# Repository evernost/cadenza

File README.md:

# cadenza
A reactive tachometer for bike.

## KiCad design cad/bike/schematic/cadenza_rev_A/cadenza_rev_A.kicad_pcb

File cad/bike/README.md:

# Cadenza project

A tachometer with reactive display (bike version)

---

## Overview

- **Type:** 
- **Domain:** Digital
- **Status:** Work in progress

---

## Features
This is an attempt to make a bike tachometer with a display providing a much better FPS compared to most tachometers you can find. 
Most of them are incredibly sluggish for reasons that are beyond me.

---

## Interfaces

### Inputs
| Name | Type | Range | Description |
|-----|------|-------|-------------|

### Outputs
| Name | Type | Description |
|------|------|-------------|
| OUT | Audio | Filtered signal |

---

## Controls

| Control | Type | Description |
|--------|------|-------------|
| Cutoff | Potentiometer | Manual cutoff frequency |
| Resonance | Potentiometer | Feedback amount |

---

## Electrical Characteristics

- **Supply voltage:** ±12V
- **Current consumption:** TBD mA
- **Signal levels:** TBD

---

## Implementation Notes
Section is TODO.

---

## Files

| File                          | Description                       |
|-------------------------------|-----------------------------------|
| `playLight_rev_A.pdf`         | Electrical schematic (PDF export) |
| `playLight_rev_A.kicad_sch`   | Schematic (KiCad 9.0.7)           |
| `playLight_rev_A.kicad_pcb`   | PCB layout (KiCad 9.0.7)          |
| `/production`                 | Production files (Gerbers + .zip) |

---

## Calibration / Tuning
None.

---

## Known Issues / TODO
None.

---

## Revision History

| Revision | Date | Notes |
|--------|------|-------|
| Rev A | 2026-06-20 | Initial prototype without USB support |
| Rev B | YYYY-MM-DD | Second version with USB logging |

---

## Tools
Designed with KiCAD 9.0.7

Grid dimensions

| Name   | Size    | Description        |
|--------|---------|--------------------|
| Grid 1 | 0.25 mm | PCB outline        |
| Grid 2 | 25 mil  | parts placement    |
| Grid 3 | 10 mil  | routing            |

---

## Related Modules
None.

---

## References
| Part type          | Reference                                                                                            | Selection criteria |
|--------------------|------------------------------------------------------------------------------------------------------|--------------------|
| LED driver         | TLC591 (TI)                                                                                          | Available in KiCAD<br>At least 8 outputs<br>Daisy-chain support |
| 7 segments display | HDSP-A401 (orange variant)<br>HDSP-7501 (red variant, high efficiency)<br>HDSP-7801 (green variant)  | Available in KiCAD<br> Bright enough for outside readbility|
| MCU                | STM32F098                                                                                            | USB OTG (for flash drive support)<br>Low pin count (for size)<br>3.3V supply|
| ON/OFF switch      | GW12LJPD                                                                                             | Available in KiCAD |

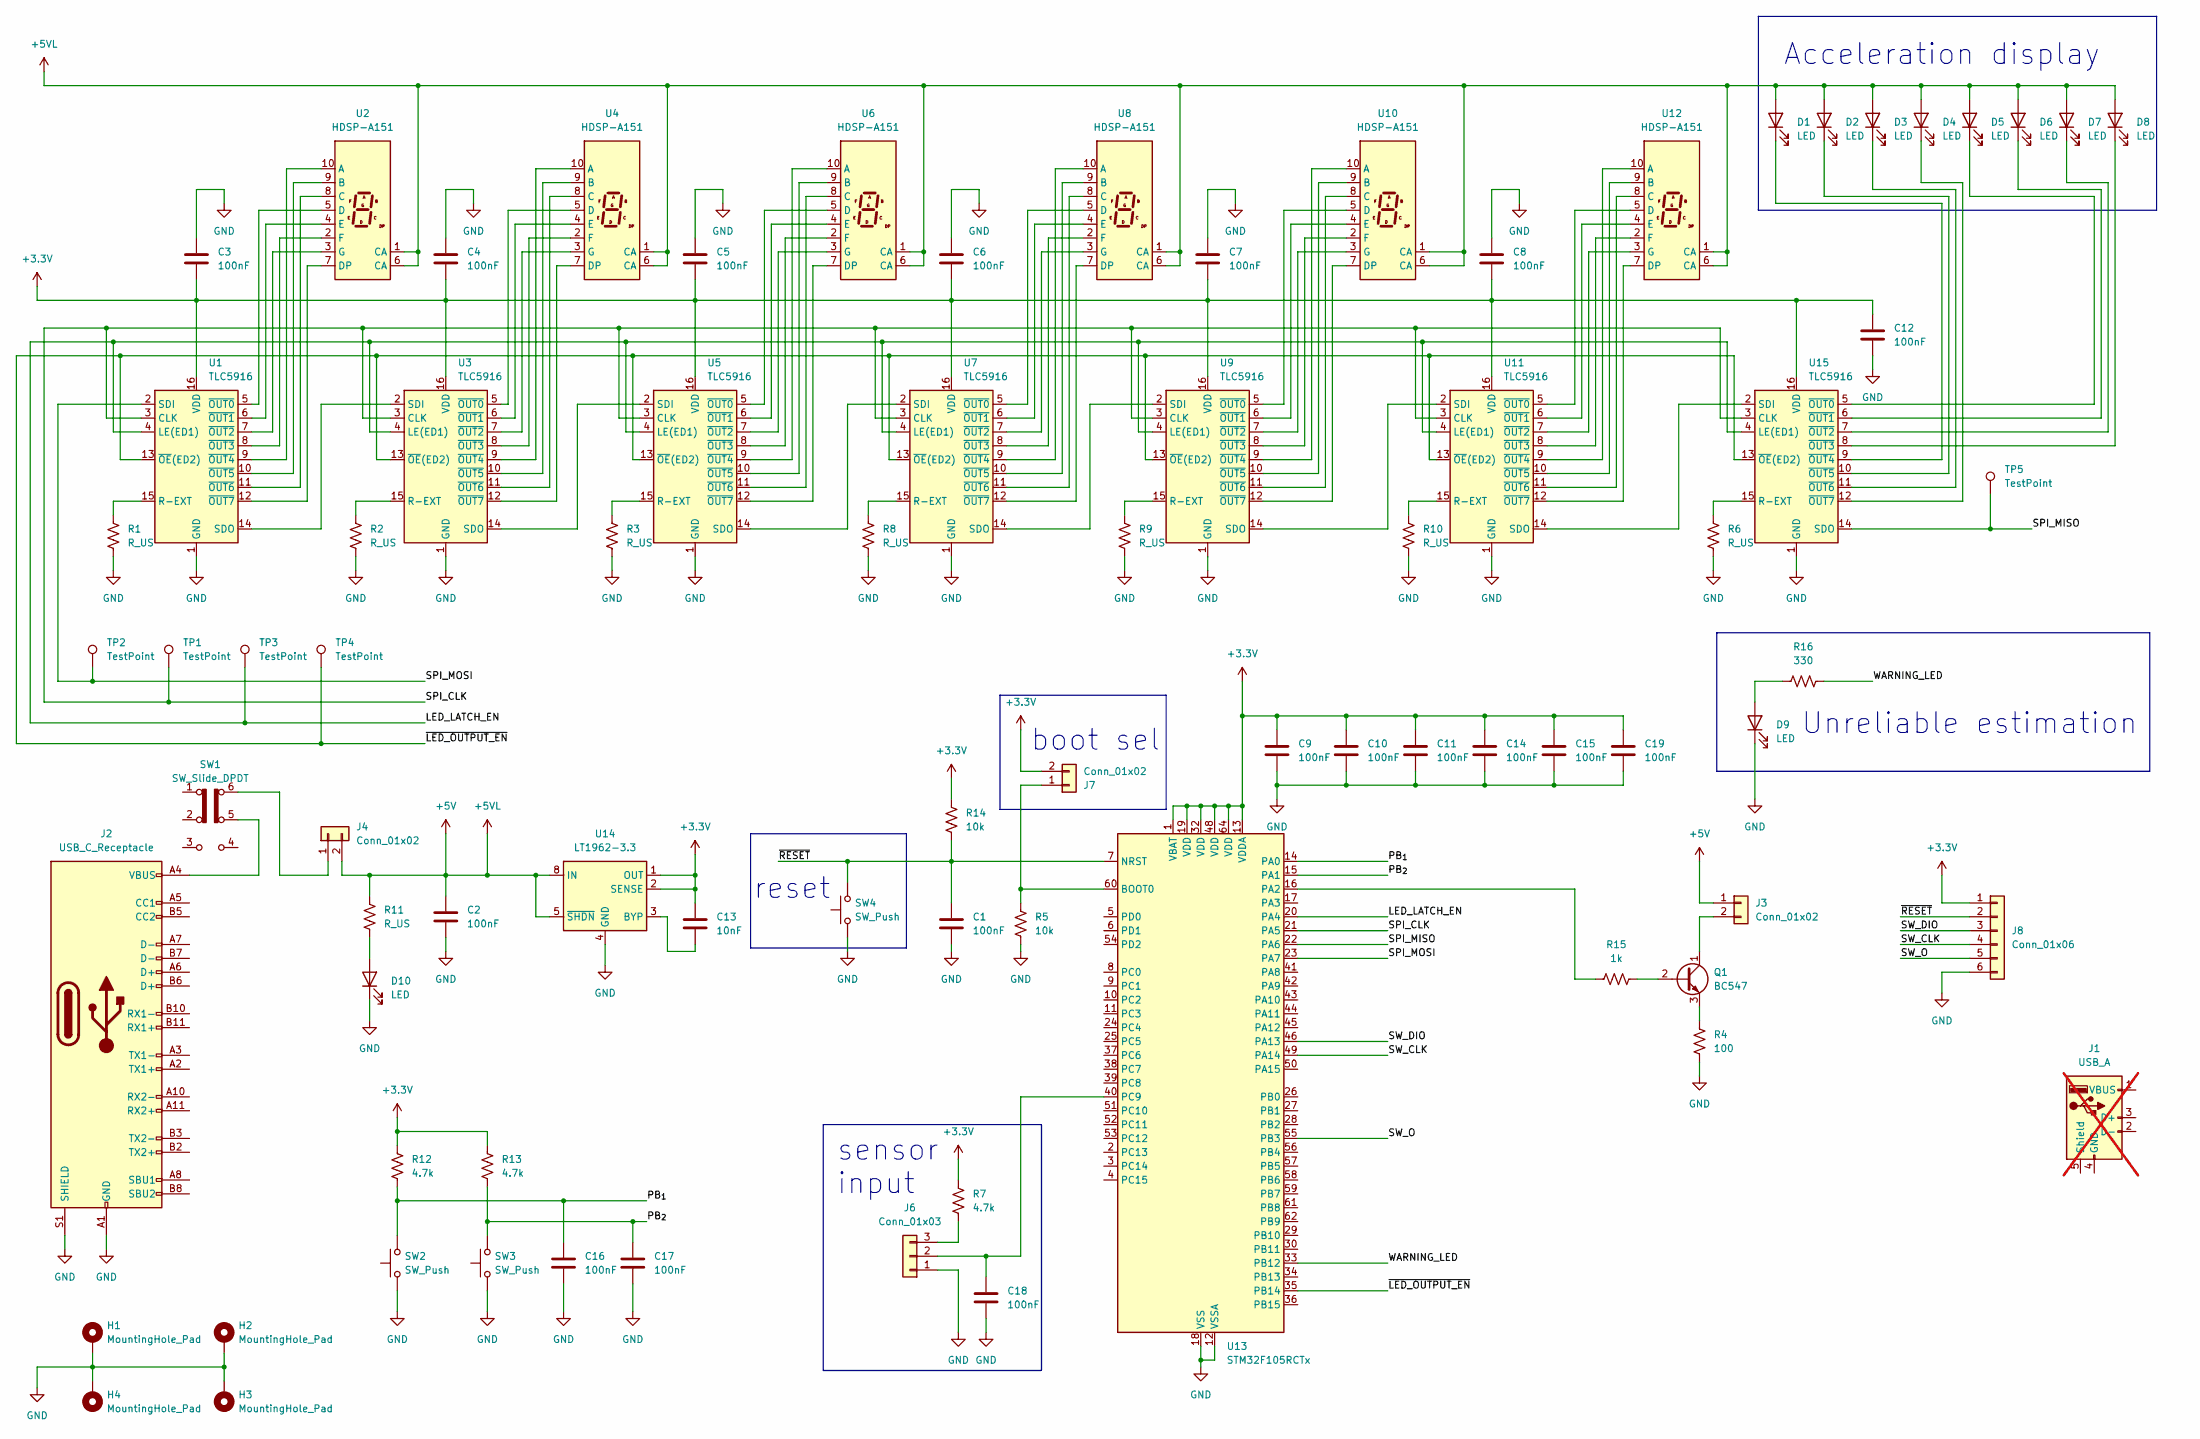
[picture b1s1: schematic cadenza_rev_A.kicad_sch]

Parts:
C1, C2, C3, C4, C5, C6, C7, C8, C9, C10, C11, C12, C14, C15, C16, C17, C18, C19: 100nF; C_0805_2012Metric_Pad1.18x1.45mm_HandSolder
C13: 10nF; C_0805_2012Metric_Pad1.18x1.45mm_HandSolder
D1, D2, D3, D4, D5, D6, D7, D8, D9, D10: LED; LED_D3.0mm
H1, H2, H3, H4: MountingHole_Pad; MountingHole_3.2mm_M3_Pad_Via
J1: USB_A; USB_A_Molex_105057_Vertical; not fitted
J2: USB_C_Receptacle; USB_C_Receptacle_Amphenol_12401548E4-2A_CircularHoles
J3, J4, J7: Conn_01x02; PinHeader_1x02_P2.54mm_Vertical
J6: Conn_01x03; PinHeader_1x03_P2.54mm_Vertical
J8: Conn_01x06; PinHeader_1x06_P2.54mm_Vertical
Q1: BC547; TO-92L_HandSolder
R1, R2, R3, R6, R8, R9, R10, R11: R_US; R_0805_2012Metric_Pad1.20x1.40mm_HandSolder
R4: 100; R_0805_2012Metric_Pad1.20x1.40mm_HandSolder
R5, R14: 10k; R_0805_2012Metric_Pad1.20x1.40mm_HandSolder
R7, R12, R13: 4.7k; R_0805_2012Metric_Pad1.20x1.40mm_HandSolder
R15: 1k; R_0805_2012Metric_Pad1.20x1.40mm_HandSolder
R16: 330; R_0805_2012Metric_Pad1.20x1.40mm_HandSolder
SW1: SW_Slide_DPDT; SW_NKK_GW12LJP
SW2, SW3, SW4: SW_Push; SW_Push_1P1T_NO_CK_KSC6xxG
TP1, TP2, TP3, TP4, TP5: TestPoint; TestPoint_Pad_D1.0mm
U1, U3, U5, U7, U9, U11, U15: TLC5916; TSSOP-16_4.4x5mm_P0.65mm
U2, U4, U6, U8, U10, U12: HDSP-A151
U13: STM32F105RCTx; LQFP-64_10x10mm_P0.5mm
U14: LT1962-3.3; MSOP-8_3x3mm_P0.65mm

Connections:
+3.3V: C3.2, C4.2, C5.2, C6.2, C7.2, C8.2, C9.1, C10.1, C11.1, C12.1, C13.1, C14.1, C15.1, C19.1, J7.2, J8.1, R7.1, R12.1, R13.1, R14.1, U1.16 (VDD), U3.16 (VDD), U5.16 (VDD), U7.16 (VDD), U9.16 (VDD), U11.16 (VDD), U13.1 (VBAT), U13.13 (VDDA), U13.19 (VDD), U13.32 (VDD), U13.48 (VDD), U13.64 (VDD), U14.1 (OUT), U14.2 (SENSE), U15.16 (VDD)
+5V: C2.1, D1.2 (A), D2.2 (A), D3.2 (A), D4.2 (A), D5.2 (A), D6.2 (A), D7.2 (A), D8.2 (A), J3.1, J4.2, R11.1, U2.1 (CA), U2.6 (CA), U4.1 (CA), U4.6 (CA), U6.1 (CA), U6.6 (CA), U8.1 (CA), U8.6 (CA), U10.1 (CA), U10.6 (CA), U12.1 (CA), U12.6 (CA), U14.5 (~SHDN), U14.8 (IN)
/LED_LATCH_EN: TP3.1 (1_1), U1.4 (LE(ED1)), U3.4 (LE(ED1)), U5.4 (LE(ED1)), U7.4 (LE(ED1)), U9.4 (LE(ED1)), U11.4 (LE(ED1)), U13.20 (PA4), U15.4 (LE(ED1))
/PB_{1}: C16.1, R12.2, SW2.2, U13.14 (PA0)
/PB_{2}: C17.1, R13.2, SW3.2, U13.15 (PA1)
/SPI_CLK: TP1.1 (1_1), U1.3 (CLK), U3.3 (CLK), U5.3 (CLK), U7.3 (CLK), U9.3 (CLK), U11.3 (CLK), U13.21 (PA5), U15.3 (CLK)
/SPI_MISO: TP5.1 (1_1), U13.22 (PA6), U15.14 (SDO)
/SPI_MOSI: TP2.1 (1_1), U1.2 (SDI), U13.23 (PA7)
/SW_CLK: J8.4, U13.49 (PA14)
/SW_DIO: J8.3, U13.46 (PA13)
/SW_O: J8.5, U13.55 (PB3)
/WARNING_LED: R16.1, U13.33 (PB12)
/~LED_OUTPUT_EN: TP4.1 (1_1), U1.13 (~OE(ED2)), U3.13 (~OE(ED2)), U5.13 (~OE(ED2)), U7.13 (~OE(ED2)), U9.13 (~OE(ED2)), U11.13 (~OE(ED2)), U13.35 (PB14), U15.13 (~OE(ED2))
/~RESET: C1.1, J8.2, R14.2, SW4.2, U13.7 (NRST)
GND: C1.2, C2.2, C3.1, C4.1, C5.1, C6.1, C7.1, C8.1, C9.2, C10.2, C11.2, C12.2, C14.2, C15.2, C16.2, C17.2, C18.2, C19.2, D9.1 (K), D10.1 (K), H1.1 (1_1), H2.1 (1_1), H3.1 (1_1), H4.1 (1_1), J2.A1 (GND), J2.A12 (GND), J2.B1 (GND), J2.B12 (GND), J2.S1 (SHIELD), J6.1, J8.6, R1.2, R2.2, R3.2, R4.2, R5.2, R6.2, R8.2, R9.2, R10.2, SW2.1, SW3.1, SW4.1, U1.1 (GND), U3.1 (GND), U5.1 (GND), U7.1 (GND), U9.1 (GND), U11.1 (GND), U13.12 (VSSA), U13.18 (VSS), U13.31 (VSS), U13.47 (VSS), U13.63 (VSS), U14.4 (GND), U15.1 (GND)
unnamed: D1.1 (K), U15.9 (~OUT4)
unnamed: D2.1 (K), U15.10 (~OUT5)
unnamed: D3.1 (K), U15.11 (~OUT6)
unnamed: D4.1 (K), U15.12 (~OUT7)
unnamed: D5.1 (K), U15.5 (~OUT0)
unnamed: D6.1 (K), U15.6 (~OUT1)
unnamed: D7.1 (K), U15.7 (~OUT2)
unnamed: D8.1 (K), U15.8 (~OUT3)
unnamed: D9.2 (A), R16.2
unnamed: D10.2 (A), R11.2
unnamed: J2.A4 (VBUS), J2.A9 (VBUS), J2.B4 (VBUS), J2.B9 (VBUS), SW1.5 (B)
unnamed: J3.2, Q1.1 (C)
unnamed: J4.1, SW1.6 (C)
unnamed: C18.1, J6.2, U13.40 (PC9)
unnamed: J6.3, R7.2
unnamed: J7.1, R5.1, U13.60 (BOOT0)
unnamed: Q1.2 (B), R15.2
unnamed: Q1.3 (E), R4.1
unnamed: R1.1, U1.15 (R-EXT)
unnamed: U1.14 (SDO), U3.2 (SDI)
unnamed: U1.5 (~OUT0), U2.5 (D)
unnamed: U1.6 (~OUT1), U2.4 (E)
unnamed: U1.7 (~OUT2), U2.3 (G)
unnamed: U1.8 (~OUT3), U2.2 (F)
unnamed: U1.9 (~OUT4), U2.10 (A)
unnamed: U1.10 (~OUT5), U2.9 (B)
unnamed: U1.11 (~OUT6), U2.8 (C)
unnamed: U1.12 (~OUT7), U2.7 (DP)
unnamed: R2.1, U3.15 (R-EXT)
unnamed: U3.14 (SDO), U5.2 (SDI)
unnamed: U3.5 (~OUT0), U4.5 (D)
unnamed: U3.6 (~OUT1), U4.4 (E)
unnamed: U3.7 (~OUT2), U4.3 (G)
unnamed: U3.8 (~OUT3), U4.2 (F)
unnamed: U3.9 (~OUT4), U4.10 (A)
unnamed: U3.10 (~OUT5), U4.9 (B)
unnamed: U3.11 (~OUT6), U4.8 (C)
unnamed: U3.12 (~OUT7), U4.7 (DP)
unnamed: R3.1, U5.15 (R-EXT)
unnamed: U5.14 (SDO), U7.2 (SDI)
unnamed: U5.5 (~OUT0), U6.5 (D)
unnamed: U5.6 (~OUT1), U6.4 (E)
unnamed: U5.7 (~OUT2), U6.3 (G)
unnamed: U5.8 (~OUT3), U6.2 (F)
unnamed: U5.9 (~OUT4), U6.10 (A)
unnamed: U5.10 (~OUT5), U6.9 (B)
unnamed: U5.11 (~OUT6), U6.8 (C)
unnamed: U5.12 (~OUT7), U6.7 (DP)
unnamed: R8.1, U7.15 (R-EXT)
unnamed: U7.14 (SDO), U9.2 (SDI)
unnamed: U7.5 (~OUT0), U8.5 (D)
unnamed: U7.6 (~OUT1), U8.4 (E)
unnamed: U7.7 (~OUT2), U8.3 (G)
unnamed: U7.8 (~OUT3), U8.2 (F)
unnamed: U7.9 (~OUT4), U8.10 (A)
unnamed: U7.10 (~OUT5), U8.9 (B)
unnamed: U7.11 (~OUT6), U8.8 (C)
unnamed: U7.12 (~OUT7), U8.7 (DP)
unnamed: R9.1, U9.15 (R-EXT)
unnamed: U9.9 (~OUT4), U10.10 (A)
unnamed: U9.10 (~OUT5), U10.9 (B)
unnamed: U9.11 (~OUT6), U10.8 (C)
unnamed: U9.5 (~OUT0), U10.5 (D)
unnamed: U9.12 (~OUT7), U10.7 (DP)
unnamed: U9.6 (~OUT1), U10.4 (E)
unnamed: U9.8 (~OUT3), U10.2 (F)
unnamed: U9.7 (~OUT2), U10.3 (G)
unnamed: R10.1, U11.15 (R-EXT)
unnamed: U9.14 (SDO), U11.2 (SDI)
unnamed: U11.14 (SDO), U15.2 (SDI)
unnamed: U11.5 (~OUT0), U12.5 (D)
unnamed: U11.6 (~OUT1), U12.4 (E)
unnamed: U11.7 (~OUT2), U12.3 (G)
unnamed: U11.8 (~OUT3), U12.2 (F)
unnamed: U11.9 (~OUT4), U12.10 (A)
unnamed: U11.10 (~OUT5), U12.9 (B)
unnamed: U11.11 (~OUT6), U12.8 (C)
unnamed: U11.12 (~OUT7), U12.7 (DP)
unnamed: R15.1, U13.16 (PA2)
unnamed: C13.2, U14.3 (BYP)
unnamed: R6.1, U15.15 (R-EXT)

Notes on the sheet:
Unreliable estimation
Acceleration display
reset
sensor input
boot sel

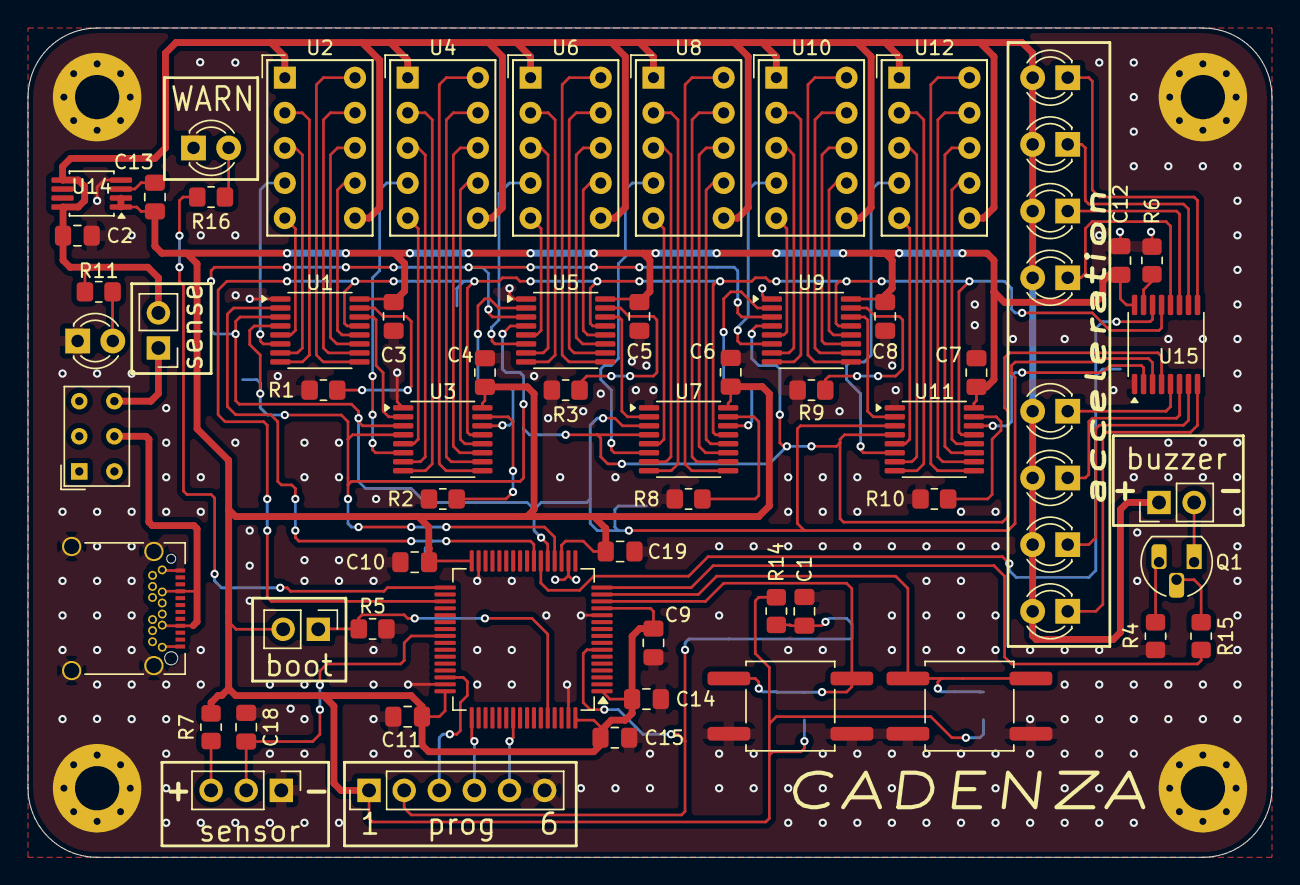
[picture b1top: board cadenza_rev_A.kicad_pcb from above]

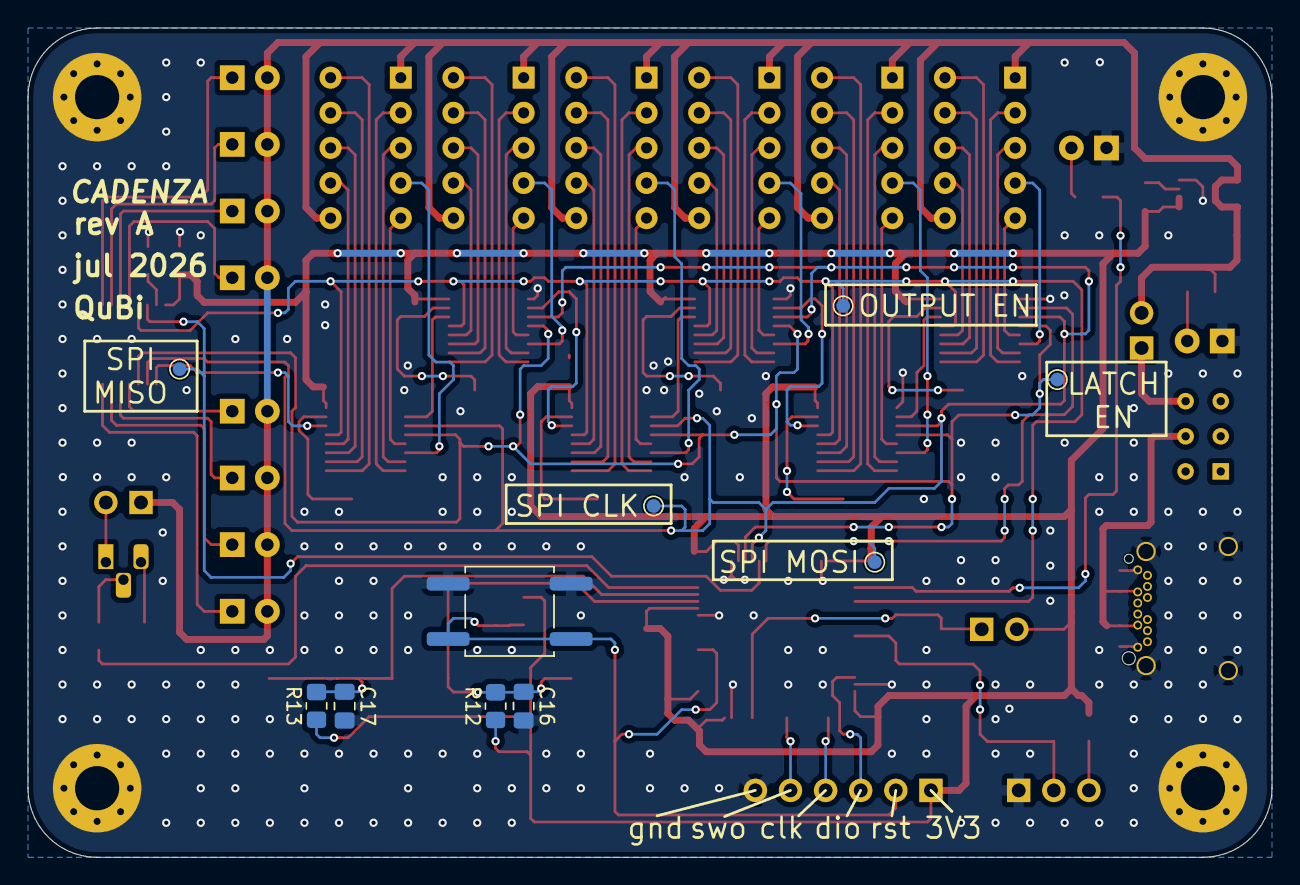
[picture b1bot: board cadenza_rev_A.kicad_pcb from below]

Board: 2 copper layers, 90.0 x 60.0 mm, 80 parts (10 on the bottom side), 96 nets.

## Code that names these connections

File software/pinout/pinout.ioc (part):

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Mcu.Name=STM32F105R(8-B-C)Tx
Mcu.Package=LQFP64
Mcu.UserName=STM32F105RCTx
PA0-WKUP.GPIOParameters=GPIO_Label
PA0-WKUP.GPIO_Label=pb_1
PA0-WKUP.Signal=GPIO_Input
PA1.GPIOParameters=GPIO_Label
PA1.GPIO_Label=pb_2
PA1.Signal=GPIO_Input
PA13.Mode=Trace_Asynchronous_SW
PA13.Signal=SYS_JTMS-SWDIO
PA14.Mode=Trace_Asynchronous_SW
PA14.Signal=SYS_JTCK-SWCLK
PA2.Signal=S_TIM2_CH3
PA4.GPIOParameters=GPIO_Label
PA4.GPIO_Label=led_latch_en
PA4.Signal=GPIO_Output
PA5.Mode=Full_Duplex_Master
PA5.Signal=SPI1_SCK
PA6.Mode=Full_Duplex_Master
PA6.Signal=SPI1_MISO
PA7.Mode=Full_Duplex_Master
PA7.Signal=SPI1_MOSI
PB12.GPIOParameters=GPIO_Label
PB12.GPIO_Label=warning_led
PB12.Signal=GPIO_Output
PB14.GPIOParameters=GPIO_Label
PB14.GPIO_Label=led_output_en_n
PB14.Signal=GPIO_Output
PB3.Mode=Trace_Asynchronous_SW
PB3.Signal=SYS_TRACESWO
board=custom

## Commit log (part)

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2026-06-19 added project
2026-06-20 added the PCB outline first proposal for the part selection
2026-06-20 added the MCU 7seg routing solution
2026-06-21 added missing parts added buzzer interface
2026-06-22 initialized the article initialized a first simulation script
2026-06-23 added the LEDs to indicate the acceleration
2026-06-24 upgraded to kicad 10
2026-06-25 included the spec graph for the kernel function
2026-06-26 proposed a first framework for the speed estimator
2026-06-27 completed a first simulation profile
2026-06-28 added the odometer function
2026-06-28 tweaked the file structure
2026-06-28 added preliminary code structure for the estimator
2026-06-30 rearranged parts placement
